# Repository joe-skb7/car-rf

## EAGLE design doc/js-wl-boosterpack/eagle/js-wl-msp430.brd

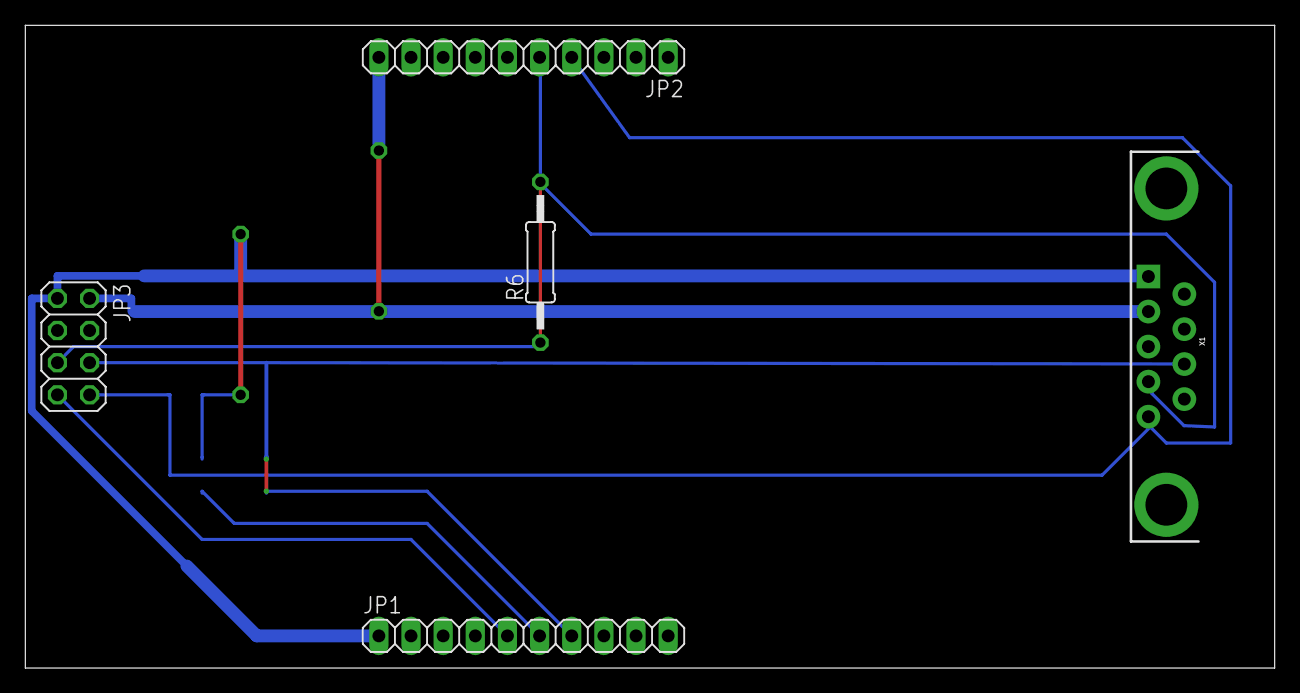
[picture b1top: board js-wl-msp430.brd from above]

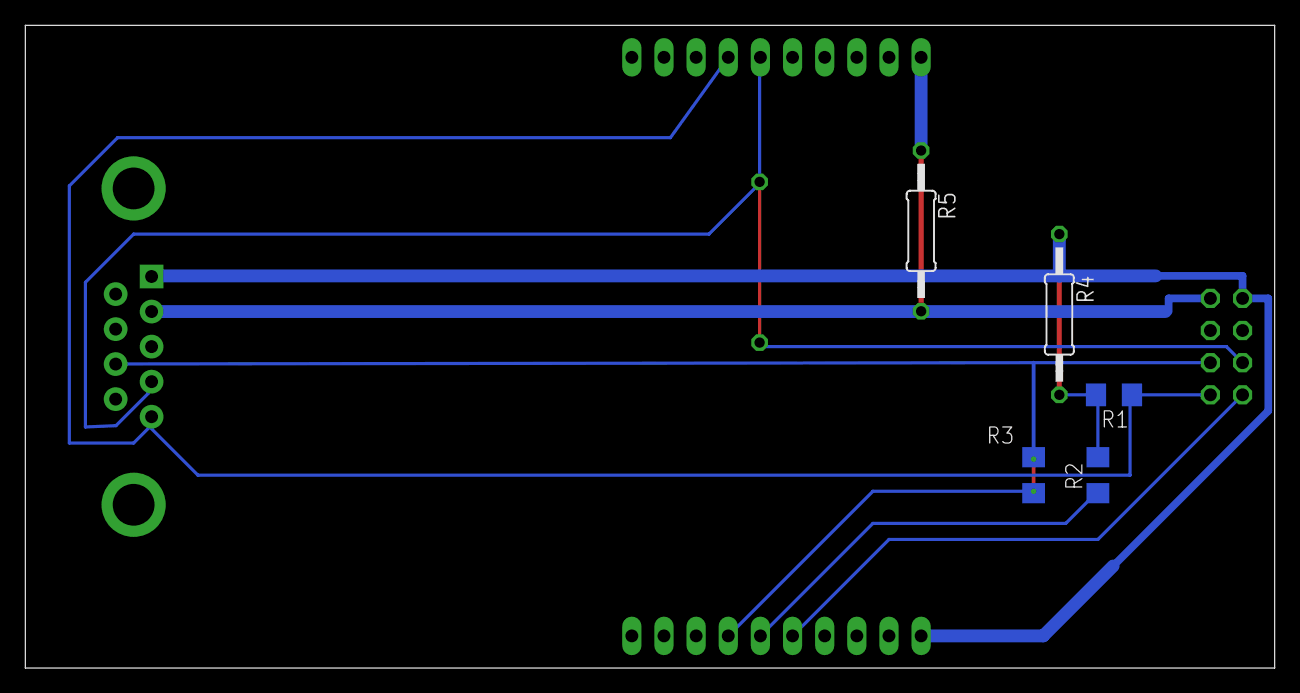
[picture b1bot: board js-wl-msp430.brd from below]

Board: 2 copper layers, 98.7 x 50.8 mm, 10 parts (5 on the bottom side), 10 nets.

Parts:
JP1, JP2: 1X10
JP3: 2X04
R1, R2: 4k7; R1206
R3: 0R; R1206
R4, R5, R6: 0R; 0207/12
X1: DB9_MALE

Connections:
GND: JP2.10, JP3.2, R5.1, R5.2, X1.4
P1.0: JP1.2, X1.6
P1.3: JP1.5, JP3.7
P1.4: JP1.6, R2.1, X1.9
P2.4: JP2.2, JP3.4
P2.5: JP2.3, JP3.3
SCLK: JP1.7, JP3.6, R3.1, R3.2, X1.7
SIMO: JP2.5, JP3.5, R6.1, R6.2, X1.2
SOMI: JP2.4, JP3.8, R1.1, X1.1
VCC: JP1.1, JP3.1, R1.2, R2.2, R4.1, R4.2, X1.5

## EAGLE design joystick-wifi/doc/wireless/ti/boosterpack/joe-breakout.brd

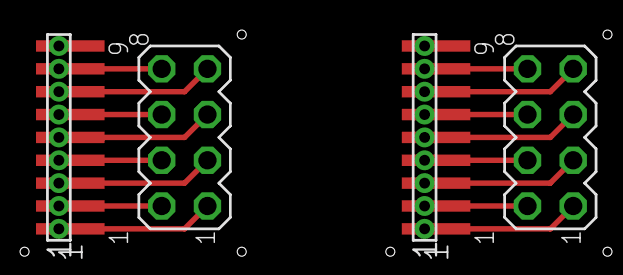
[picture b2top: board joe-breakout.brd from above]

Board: 2 copper layers, 6 parts (0 on the bottom side), 18 nets.

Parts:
J1, J3: MA09-1-05-SMD_LG
J2, J10: FE04-2; MA04-2-NOTXT
J4, J14: MA09-1-0.05-RG

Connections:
GND: J3.6, J10.6, J14.6
GND1: J1.6, J2.6, J4.6
unnamed: J3.1, J10.1, J14.1
unnamed: J3.2, J10.2, J14.2
unnamed: J3.3, J10.3, J14.3
unnamed: J3.4, J10.4, J14.4
unnamed: J3.5, J10.5, J14.5
unnamed: J1.1, J2.1, J4.1
unnamed: J3.7, J10.7, J14.7
unnamed: J3.8, J10.8, J14.8
unnamed: J1.2, J2.2, J4.2
unnamed: J1.3, J2.3, J4.3
unnamed: J1.4, J2.4, J4.4
unnamed: J1.5, J2.5, J4.5
unnamed: J1.7, J2.7, J4.7
unnamed: J1.8, J2.8, J4.8
unnamed: J1.9, J4.9
unnamed: J3.9, J14.9

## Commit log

2013-08-31 initial commit
    By now we have joystick and UART (PC serial console) working.
2013-08-31 makefile: fix PROGRAMMER variable using
2013-08-31 Added .gitignore file
2013-08-31 Moved ds2 and spi code to their corresponding .h and .c files
2013-08-31 Moved some functions from ds2 to spi
2013-08-31 Ignore *.swp files
2013-08-31 Ignored .cscope
2013-08-31 Moved interrupt stuff to interrupts.c
2013-08-31 cc2500: improve cc2500 breakout PCB
    Arrange two same PCBs horizontally (instead of vertical layout)
    so that it can be printed with economy of PCB tape.
2013-08-31 ds2: fix sparse warning
    Thi patch fixes next sparse warning:
    "./src/ds2/ds2.c:3:6: warning: symbol 'ds2_poll_buttons_sync' was not declared.
    Should it be static?"
2013-08-31 makefile: check static analyzer parameters
    With "-quiet" parameter splint gave such a warning:
    "Command Line: Setting -quiet redundant with current value"
    So remove "-quiet" for now.
2013-08-31 interrupts: fix static analyzer warnings
    Fix next warnings gotten from splint:
    src/interrupts.c: (in function usci0rx_isr)
    src/interrupts.c:35:17: Function usci0a_rx_cb expects arg 1 to be uint8_t gets
    char: (char)UCA0RXBUF
    src/interrupts.c:41:17: Function usci0b_rx_cb expects arg 1 to be uint8_t gets
    char: (char)UCB0RXBUF
2013-08-31 cc2500: add new useful links
2013-08-31 joystick: remove duplicate uart scheme
2013-08-31 joystick: move joystick files 1 level top
    After removing duplicate scheme, there is 1 redundant dir level.
    Fix it.
2013-08-31 doc: move doc files to dedicated directory
2013-08-31 cc2500: move urls file to dedicated doc directory
2013-08-31 git: move .gitignore on the top
    So that listed files can be ignored in each project.
2013-09-01 rearrange project stucture
    Project structure was a way redundant. Fix it.
2013-09-01 common: remove redundant ";" in do ... while (0) macro
2013-09-01 cc2500: update documentation
    CC2500 module documentation was incorrect (we have different module).
    Fix this documentation to being reliable.
2013-09-01 doc: sync BOM to be up-to-date
2013-09-01 doc: convert BOM to CSV
    CSV is text format and should be better for git that ODS.
2013-09-01 interrupts: unify coding style
2013-09-01 ds2: comment out declaration of commented out function
    Comment out ds2_handshake() declaration as it's definition also
    commented out.
    Dima, do smth with this crap.
2013-09-01 spi: coding issues
2013-09-01 uart: fix comment
2013-09-01 spi: mark debug code for remove
2013-09-01 spi: coding style: general headers on top
2013-09-01 spi: mark debug header to remove
2013-09-01 uart: coding style: fix erroneous comment
2013-09-03 doc: update "ideas"
    add mechanical hand note
2013-09-03 car: doc: add chassis documentation
2013-09-03 car: doc: add motors specs
2013-09-03 car: doc: add motor driver (HW) documentation
2013-09-03 doc: update actual motor driver at BOM
2013-09-03 doc: update BOM to be up-to-date
2013-09-03 car: doc: add URL for motor booster-pack
    Information about motor booster-pack for MSP430 may be useful
    in future, so just leave link for it in docs.
2013-09-07 doc: update BOM
    Batteries and charger are bought.
2013-09-08 car: add test code for car chassis
    This code allows car only to move back and forth.
    It's just for test to be sure that motors and driver works and scheme
    assembled correct.
2013-09-08 doc: add wishes to BOM
2013-09-08 car: make motor action synchronous
2013-09-08 car: add comments to improve code readability
2013-09-08 car: rename variable name to more intuitive
2013-09-08 doc: update BOM
    Update BOM, adding all the items were bought at Kardachi.
2013-09-09 car: split vehicle code into 2 separate module
    Now we have 2 modules:
    - motor-driver: implements low-level control of motor driver
    - vehicle: implements high-level commands ("forward", "stop" etc)
2013-09-28 wireless: relocate ti wl module documentation
2013-09-28 wireless: add nRF24L01 documentation
    nRF24L01 chip and TK0348 module specifications.
2013-09-28 car: pull down port 3 lines as recommended in datasheet
    From datasheet:
    "NOTE: The pulldown resistors of port P3 should be
    enabled by setting P3REN.x = 1."
2013-09-28 joystick: pull down port 3 lines as recommended in datasheet
    From datasheet:
    "NOTE: The pulldown resistors of port P3 should be
    enabled by setting P3REN.x = 1."
2013-09-28 wireless: add spi configuration from Grace
2013-09-28 doc: add protothread links to ideas
2013-09-28 wireless: add useful links to doc
2013-10-19 joystick: add joystick wifi boosterpack
    Add Eagle files (PCB+Schematic) for "Wireless Joystick Boosterpack".
    It's a board with sockets for:
    - MSP430 Launchpad
    - Joystick (joystick socket needs to be replaced by DB9-F socket)
    - Wireless module (NRF24L01)
    This board just connects MSP430 Launchpad with joystick and Wireless
2013-10-19 doc: move common documentation from joystic doc
2013-10-19 doc: remove unused docs
    We are decided to use NRF24L01 instead of CC2500. So CC2500 docs
    can be removed now.
2013-10-19 doc: move all docs to common
    It would be more convenient to keep all docs at one place.
    So move docs from "car" project and "joystick" project to one place
    (top dir doc).
2013-10-19 doc: yet another rearrangement
    Make docs more accesible.
2013-10-19 doc: move eagle files back to "eagle" dir
    New files will be added soon, so prepare for this.
2013-10-19 doc: add joystick socket soldering instructions
2013-10-19 doc: add new ideas
2013-10-19 doc: add wishes (which stuff to order in future)
2013-10-20 doc: add TODO for joystick boosterpack
    PCB was made in wrong way. It works now only with
    JP1/JP2 extenders. Rework it later.
2013-10-20 libspi: add init files
2013-10-20 Joystick: wireless implementation
2013-10-20 doc: add general msp430 pin usage scheme
2013-10-20 libspi: remove it
    See common/{src/include}/spi for SPI driver code.
2013-10-20 doc: add TODO file
2013-10-20 doc: fix motor driver module view
    Fix and enhance motor driver view:
    - Fix 12V/5V marks
    - Add OUT1..OUT4 marks
2013-10-20 doc: add car schemes
2013-10-21 car: simplify code
2013-10-21 car: fix incorrect motor driver code
2013-10-21 car: add "vehicle_move()" function
2013-10-21 car: make car being controlled by wireless joystick
2013-10-21 doc: update car scheme
2013-11-10 car: fix interrupt variable
    Use "volatile" keyword for global variables involved to interrupt
    routine.
2013-11-10 Unset msp interrupt flag before unsetting wl module interrupt flag
2013-11-10 Do not send button states if nothing changed
2013-11-10 wl: fix global interrupt variable
    Use "volatile" keyword for global variables used in interrupt.
2013-11-10 doc: motor-suppressor: add files
    Since DC motors noise issue was revealed, there is need to
    develop noise suppressors. Info found in net was added.
2013-11-10 doc: motor-driver: fix 01
    Add ceramic capacitors (100n) to Vs and Vss line, as recommended
    by datasheet.
2013-11-11 doc: motor-suppressor: add detailed explanation of issue
2013-11-16 doc: motor-suppressor: add a bit more details
2013-11-16 doc: motor-suppressor: rearrange doc files
2013-11-16 doc: motor-suppressor: add grounding recommendations
2014-01-07 car: Makefile: improve checking
2014-01-07 car: fix debug code
2014-01-07 uart: fix clang static analyzer warning
    Fix this warning:
    scan-build: Using '/usr/bin/clang' for static analysis
    ../common/src/uart/uart.c:62:2: warning: Undefined or garbage value
    returned to caller
    return ret;
2014-01-07 TODO: add useful link
2014-01-07 Makefiles: sync makefiles in car/ and joystick/ projects
2014-01-07 doc: add servo docs
2014-01-07 doc: add inductor info to motor-suppressor docs
2014-01-07 car: add some temporary code just for sync purposes
2018-05-06 Add GPLv3 license file

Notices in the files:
parts and their libraries:
SparkFun: Licensing: CC v3.0 Share-Alike You are welcome to use this library for commercial purposes.
